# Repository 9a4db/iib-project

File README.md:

# Matt's 4th Year Project

## GPSDO
This contains the design files and firmware for a GPS disciplined oscillator. It combines the frequency reference from a Ublox MAX-M8Q GPS module with a low jitter timing reference to create a very stable and accurate user defined frequency reference. There are two identical buffered clock outputs as well as a 1Hz PPS. The PPS output is used as a timing reference for synchronizing the output streams of multiple independent SDRs. There is also a command line application to view the status of the GPS and PLL live.

## Lime-SDR
This folder contains various resources such as the modified gateware running on the Lime Mini's MAX10 FPGA, the design files for a small PCB to break the 0.1" header on the Lime Mini out to an SMA connector, and a setup guide.

## Software
This folder contains some prototype applications written in C++ that make use of the LimeSuite LMS API.

### pps_rx_sync
This program produces an output file each second that contains a header followed by a buffer of interleaved IQ samples in int16_t format. The header specifies the index of the first sample in the buffer and the index of the sample corresponding to the PPS trigger event as well as a unix timestamp for the file.

### pps_tx_sync
This program transmitts a buffer of samples once per second, with the transmission occuring a predefined number of samples after the PPS event. Assuming there is some external loopback path the program also records the TX event and writes this out to file, along with the relevant metadata.

### tx_testing
This program demonstrates how to succesfully specify at what sample the transmission of a buffer should occur, and how to the record the transmission in order to verify when it occured, which initially proved problematic!

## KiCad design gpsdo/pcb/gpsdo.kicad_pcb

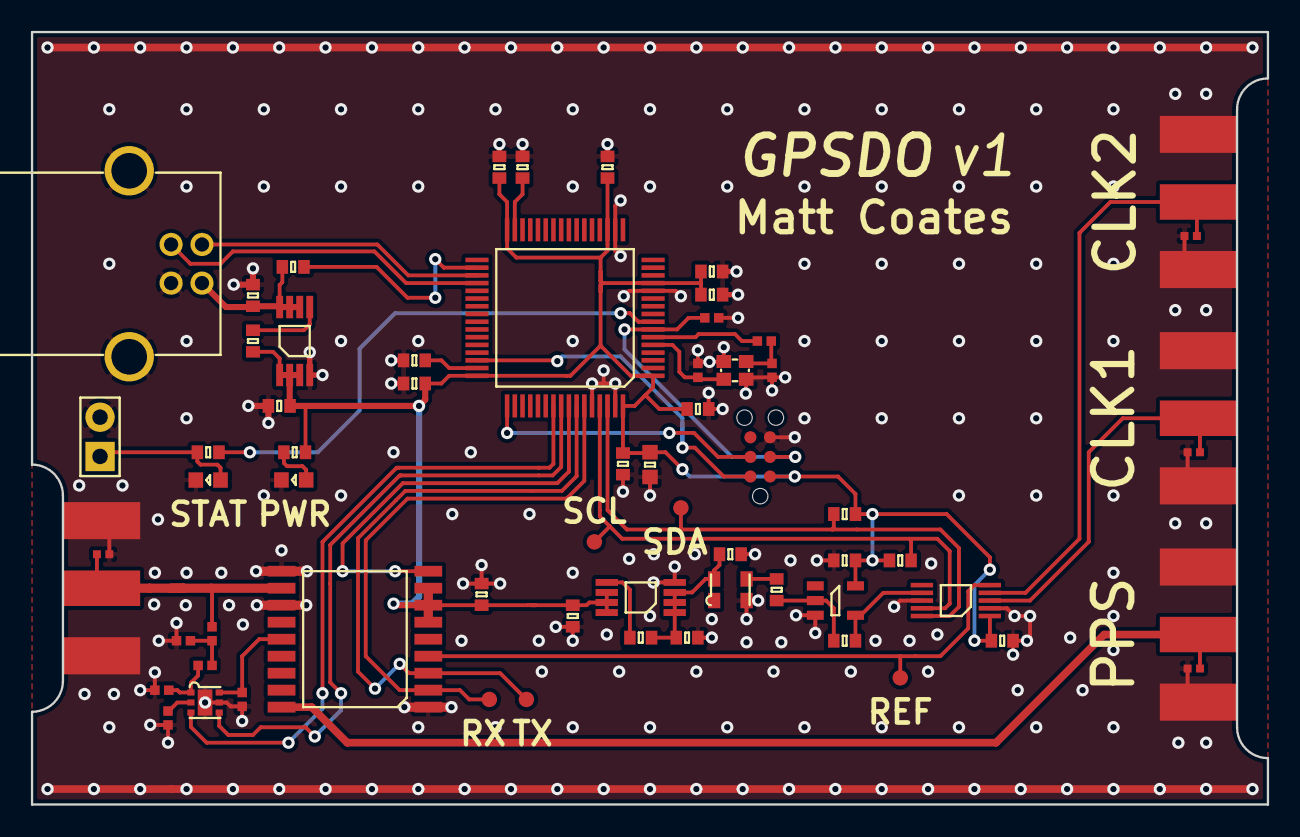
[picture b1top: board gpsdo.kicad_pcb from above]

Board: 2 copper layers, 80.0 x 50.0 mm, 64 parts (0 on the bottom side), 39 nets.

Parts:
C1, C12, C17, C23, C25: 1u; 0603-L
C2, C27: 100n; 0402
C3, C5: 10p; 0402
C4, C6, C9, C11, C13, C14, C15, C20, C21: 100n; 0603-L
C7, C8: 2u2; 0603-L
C10, C24: 10n; 0603-L
C16: 4u7; 0603
C18, C19: 1n; 0603-L
C22, C26: 1u; 0402
D1, D2, D3, D4: ESD_DIODE; 0402-L
D5, D6: LED; 0603-LED
IC1, IC6: ADP3335; MSOP-8
IC2: STM32F405RxTx; LQFP-64
IC3: NC7SZ04; SOT-23-5
IC4: CS2100-CP; MSOP-10
IC5: MAX-M8Q
IC7: NCP380; DFN-6-EP-ONSEMI
J1: LED; SIL-254P-02
L1: 27nH; 0402
P1: SWD_TC; TC2030-NL
P2, P3, P4, P5: SMA; SMA-EDGE
P6: USB-B; USB-B-SKT
R1: 100; 0402
R2, R4: 10K; 0603-L
R3: 1M; 0603-L
R5: 110k; 0402
R6: 10; 0402
R7, R8: 120; 0603-L
R9: 1K; 0603-L
TP1, TP2, TP3, TP4, TP5: TESTPAD
Y1: 26M; XTAL-20x16
Y2: 26M TCXO; XTAL-25x20

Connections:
1v8: C10.1, C12.1, C14.2, IC1.1, IC1.2, IC1.3, Y2.4
3v3: C1.1, C4.2, C6.2, C9.2, C11.2, C13.2, C15.2, C16.2, C17.1, C18.2, C20.2, C21.2, C24.1, C25.1, IC1.6, IC1.7, IC1.8, IC2.1, IC2.13, IC2.19, IC2.32, IC2.48, IC2.64, IC3.5, IC4.1, IC5.6, IC5.7, IC5.8, IC6.1, IC6.2, IC6.3, P1.1, R2.2, R4.2, R8.2
5v: C23.1, IC6.6, IC6.7, IC6.8, P6.1, R9.1
/CLK_OUT_1: D2.1, IC4.3, P3.1
/CLK_OUT_2: D3.1, IC4.4, P4.1
/GPS_PPS: D1.1, IC5.18, P2.1
/GPS_RF: D4.1, IC5.11, L1.2, P5.1
/GPS_RST: IC2.57, IC5.9
/GPS_TIM1: IC4.5, IC5.4, TP5.1
/I2C1_SCL: IC2.61, IC4.9, R4.1, TP2.1
/I2C1_SDA: IC2.62, IC4.10, R2.1, TP1.1
/OTG_HS_DM: IC2.35, P6.2
/OTG_HS_DP: IC2.36, P6.3
/OTG_HS_VBUS: IC2.34, R9.2
/STATUS: IC2.8, R7.2
/SWDCLK: IC2.49, P1.4
/SWDIO: IC2.46, P1.2
/USART1_RX: IC2.59, IC5.2, TP4.1
/USART1_TX: IC2.58, IC5.3, TP3.1
/~ANT_EN: IC2.56, IC7.4
/~FLAG: IC2.55, IC7.3
/~RST: C2.1, IC2.7, P1.3
GND: C1.2, C2.2, C3.1, C4.1, C5.2, C6.1, C7.1, C8.2, C9.1, C11.1, C12.2, C13.1, C14.1, C15.1, C16.1, C17.2, C18.1, C20.1, C21.1, C22.2, C23.2, C25.2, C26.2, C27.1, D1.2, D2.2, D3.2, D4.2, D5.1, D6.1, IC1.4, IC2.12, IC2.18, IC2.60, IC2.63, IC3.3, IC4.2, IC4.8, IC5.1, IC5.10, IC5.12, IC6.4, IC7.5, IC7.EP, J1.2, P1.5, P2.2, P3.2, P4.2, P5.2, P6.4, P6.S, R5.1, Y1.2, Y1.4, Y2.2
unnamed: C3.2, IC2.5, Y1.1
unnamed: C5.1, R1.1, Y1.3
unnamed: C7.2, IC2.31
unnamed: C8.1, IC2.47
unnamed: C10.2, IC1.5
unnamed: C19.1, IC3.2, R3.2
unnamed: C19.2, Y2.3
unnamed: C22.1, IC5.14, IC7.6
unnamed: C24.2, IC6.5
unnamed: C26.1, IC7.1, R6.2
unnamed: C27.2, L1.1, R6.1
unnamed: D5.2, J1.1, R7.1
unnamed: D6.2, R8.1
unnamed: IC2.6, R1.2
unnamed: IC3.4, IC4.7, R3.1
unnamed: IC7.2, R5.2

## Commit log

2018-06-10 added setup guide
2018-06-10 started gpsdo module
2018-06-11 finished pcb
2018-06-11 added external led
2018-06-12 added firmware for gpsdo, tested with toad. GPS frequency reference and usb upload working well, just need to sort out pll and decide how much flexibility, if any, there should be in the output clock
2018-06-12 added git ignore
2018-06-16 added bom subs and gerbers zip
2018-07-11 generated board.h, tweaked gps config, cs2100 ratio value and PLL aux output. Need to finish status indication.
2018-07-11 tweaked formatting
2018-09-06 added status and clk out
2018-09-14 changed pps oulse width to 40us. Also added modifed FPGA image to do PPS sync, and python scripts to count samples between PPS events.
2018-09-16 finished gpio to sma pcb
2018-09-17 changed ref clk to 40mhz
2018-09-18 started sdr app
2018-09-18 tested pps delta
2018-09-18 app progress
2018-09-20 changed sample plot
2018-09-20 now write out unique file of n buffers with header on each pps event and can process in python accordingly
2018-09-21 enabled test sig
2018-09-21 fixed stack overflow
2018-09-21 added pll status to telemetry
2018-09-21 oved folders
2018-09-23 added file buffer
2018-09-23 added transciever_setup
2018-09-24 tx example working
2018-09-24 tx/rx kind of works
2018-09-24 sync tx works kinda
2018-09-24 tx sync broken
2018-09-24 tx occuring late
2018-09-24 debugging TX
2018-09-26 tx testing
2018-09-26 testing continues...
2018-09-26 tx seems to work maybe
2018-09-26 scheduled tx of single buffer appears to work
2018-09-27 tx progress
2018-09-27 added multiple tx events
2018-09-27 converted RX to I12 format
2018-09-27 rx working with ext ref
2018-09-28 tx sync works
2018-09-28 Added Lime-Mini gateware
2018-09-28 PPS scheduled TX works!
2018-09-28 updated comments/readme
